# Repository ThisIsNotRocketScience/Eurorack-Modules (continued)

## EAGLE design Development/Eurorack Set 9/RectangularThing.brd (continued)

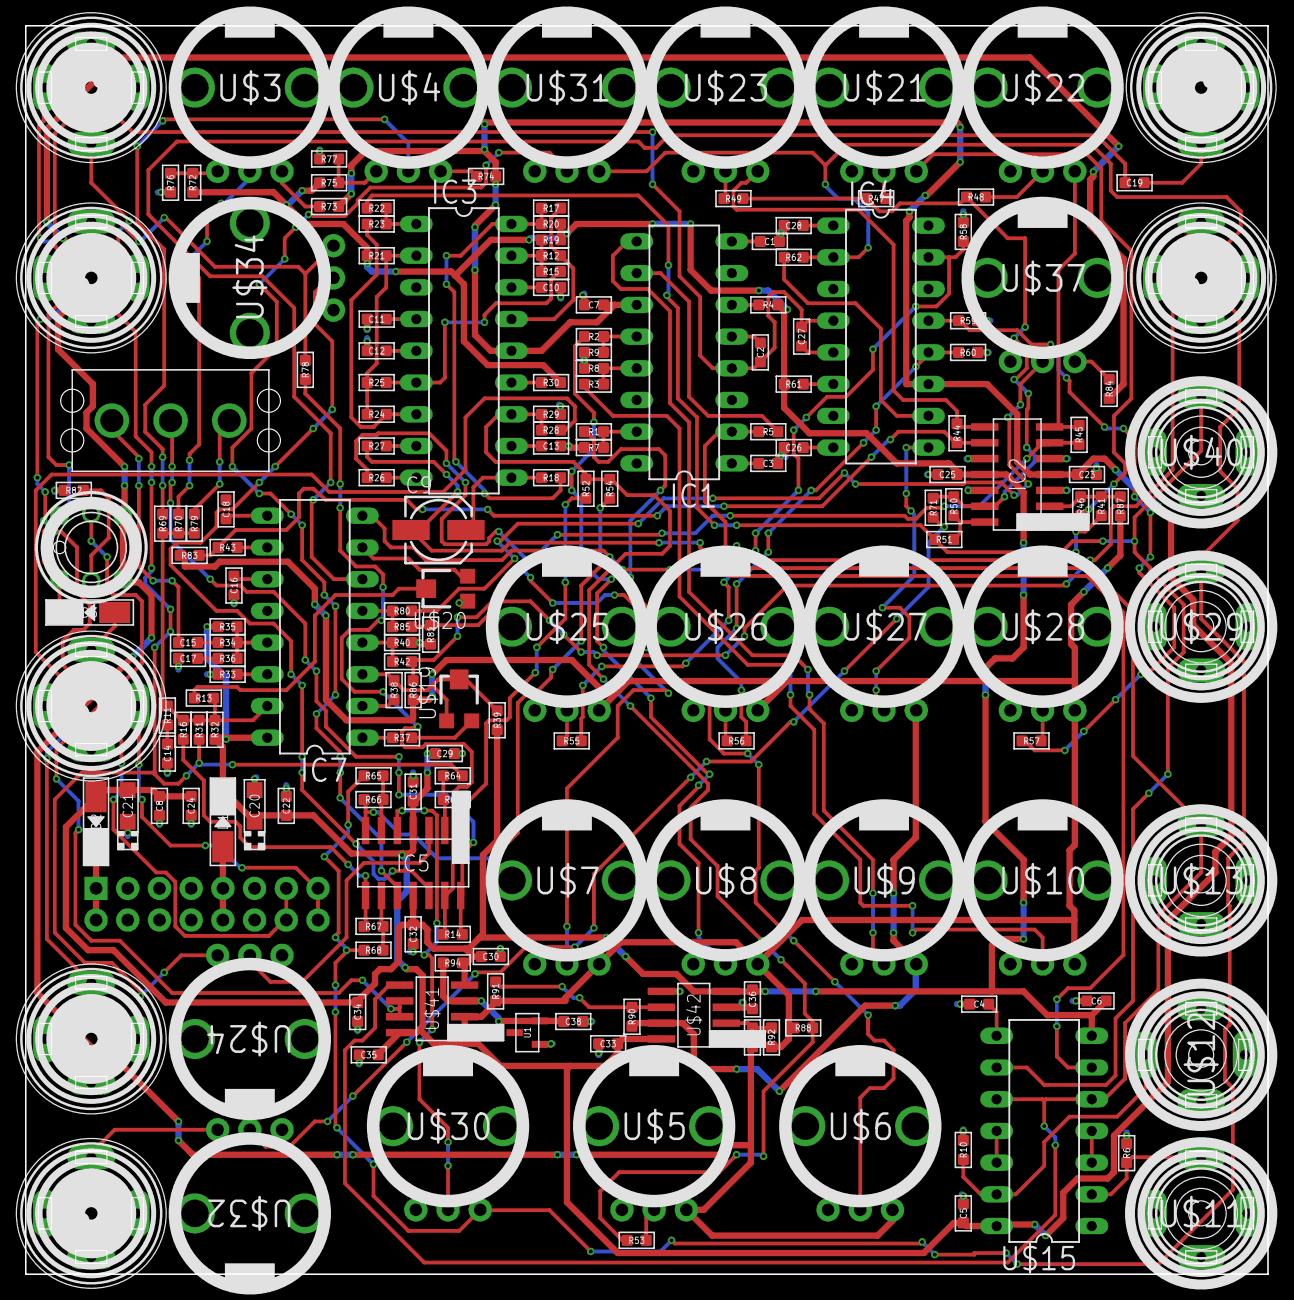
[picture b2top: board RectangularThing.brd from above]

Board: 2 copper layers, 99.5 x 100.0 mm, 182 parts (1 on the bottom side), 127 nets.

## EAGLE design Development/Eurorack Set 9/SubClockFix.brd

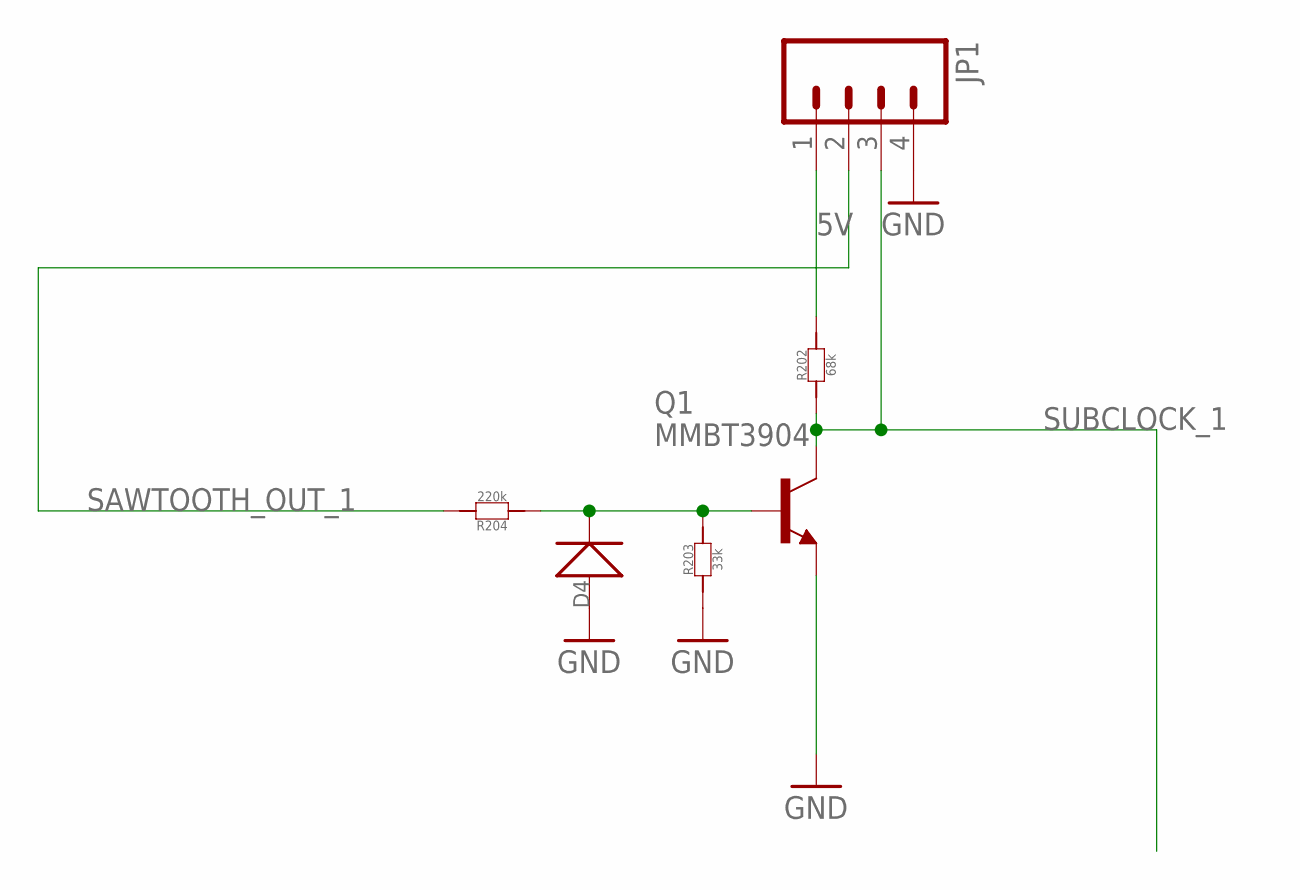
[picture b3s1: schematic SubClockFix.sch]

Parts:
D4: D-SMA; DO-214AC
JP1: M04PTH; 1X04
Q1: MMBT3904; SOT23-BEC; MPN PMBT3904,215
R202: 68k; R0603
R203: 33k; R0603
R204: 220k; R0603

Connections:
5V: JP1.1, R202.2
GND: D4.1 (+), JP1.4, Q1.E, R203.1
unnamed: D4.2 (-), Q1.B, R203.2, R204.1
SAWTOOTH_OUT_1: JP1.2, R204.2
SUBCLOCK_1: JP1.3, Q1.C, R202.1

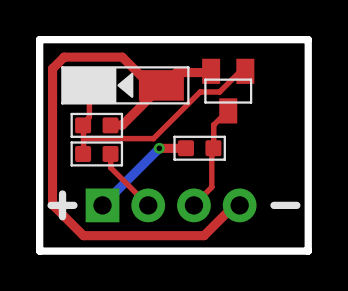
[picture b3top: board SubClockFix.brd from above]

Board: 2 copper layers, 14.9 x 11.7 mm, 6 parts (0 on the bottom side), 5 nets.

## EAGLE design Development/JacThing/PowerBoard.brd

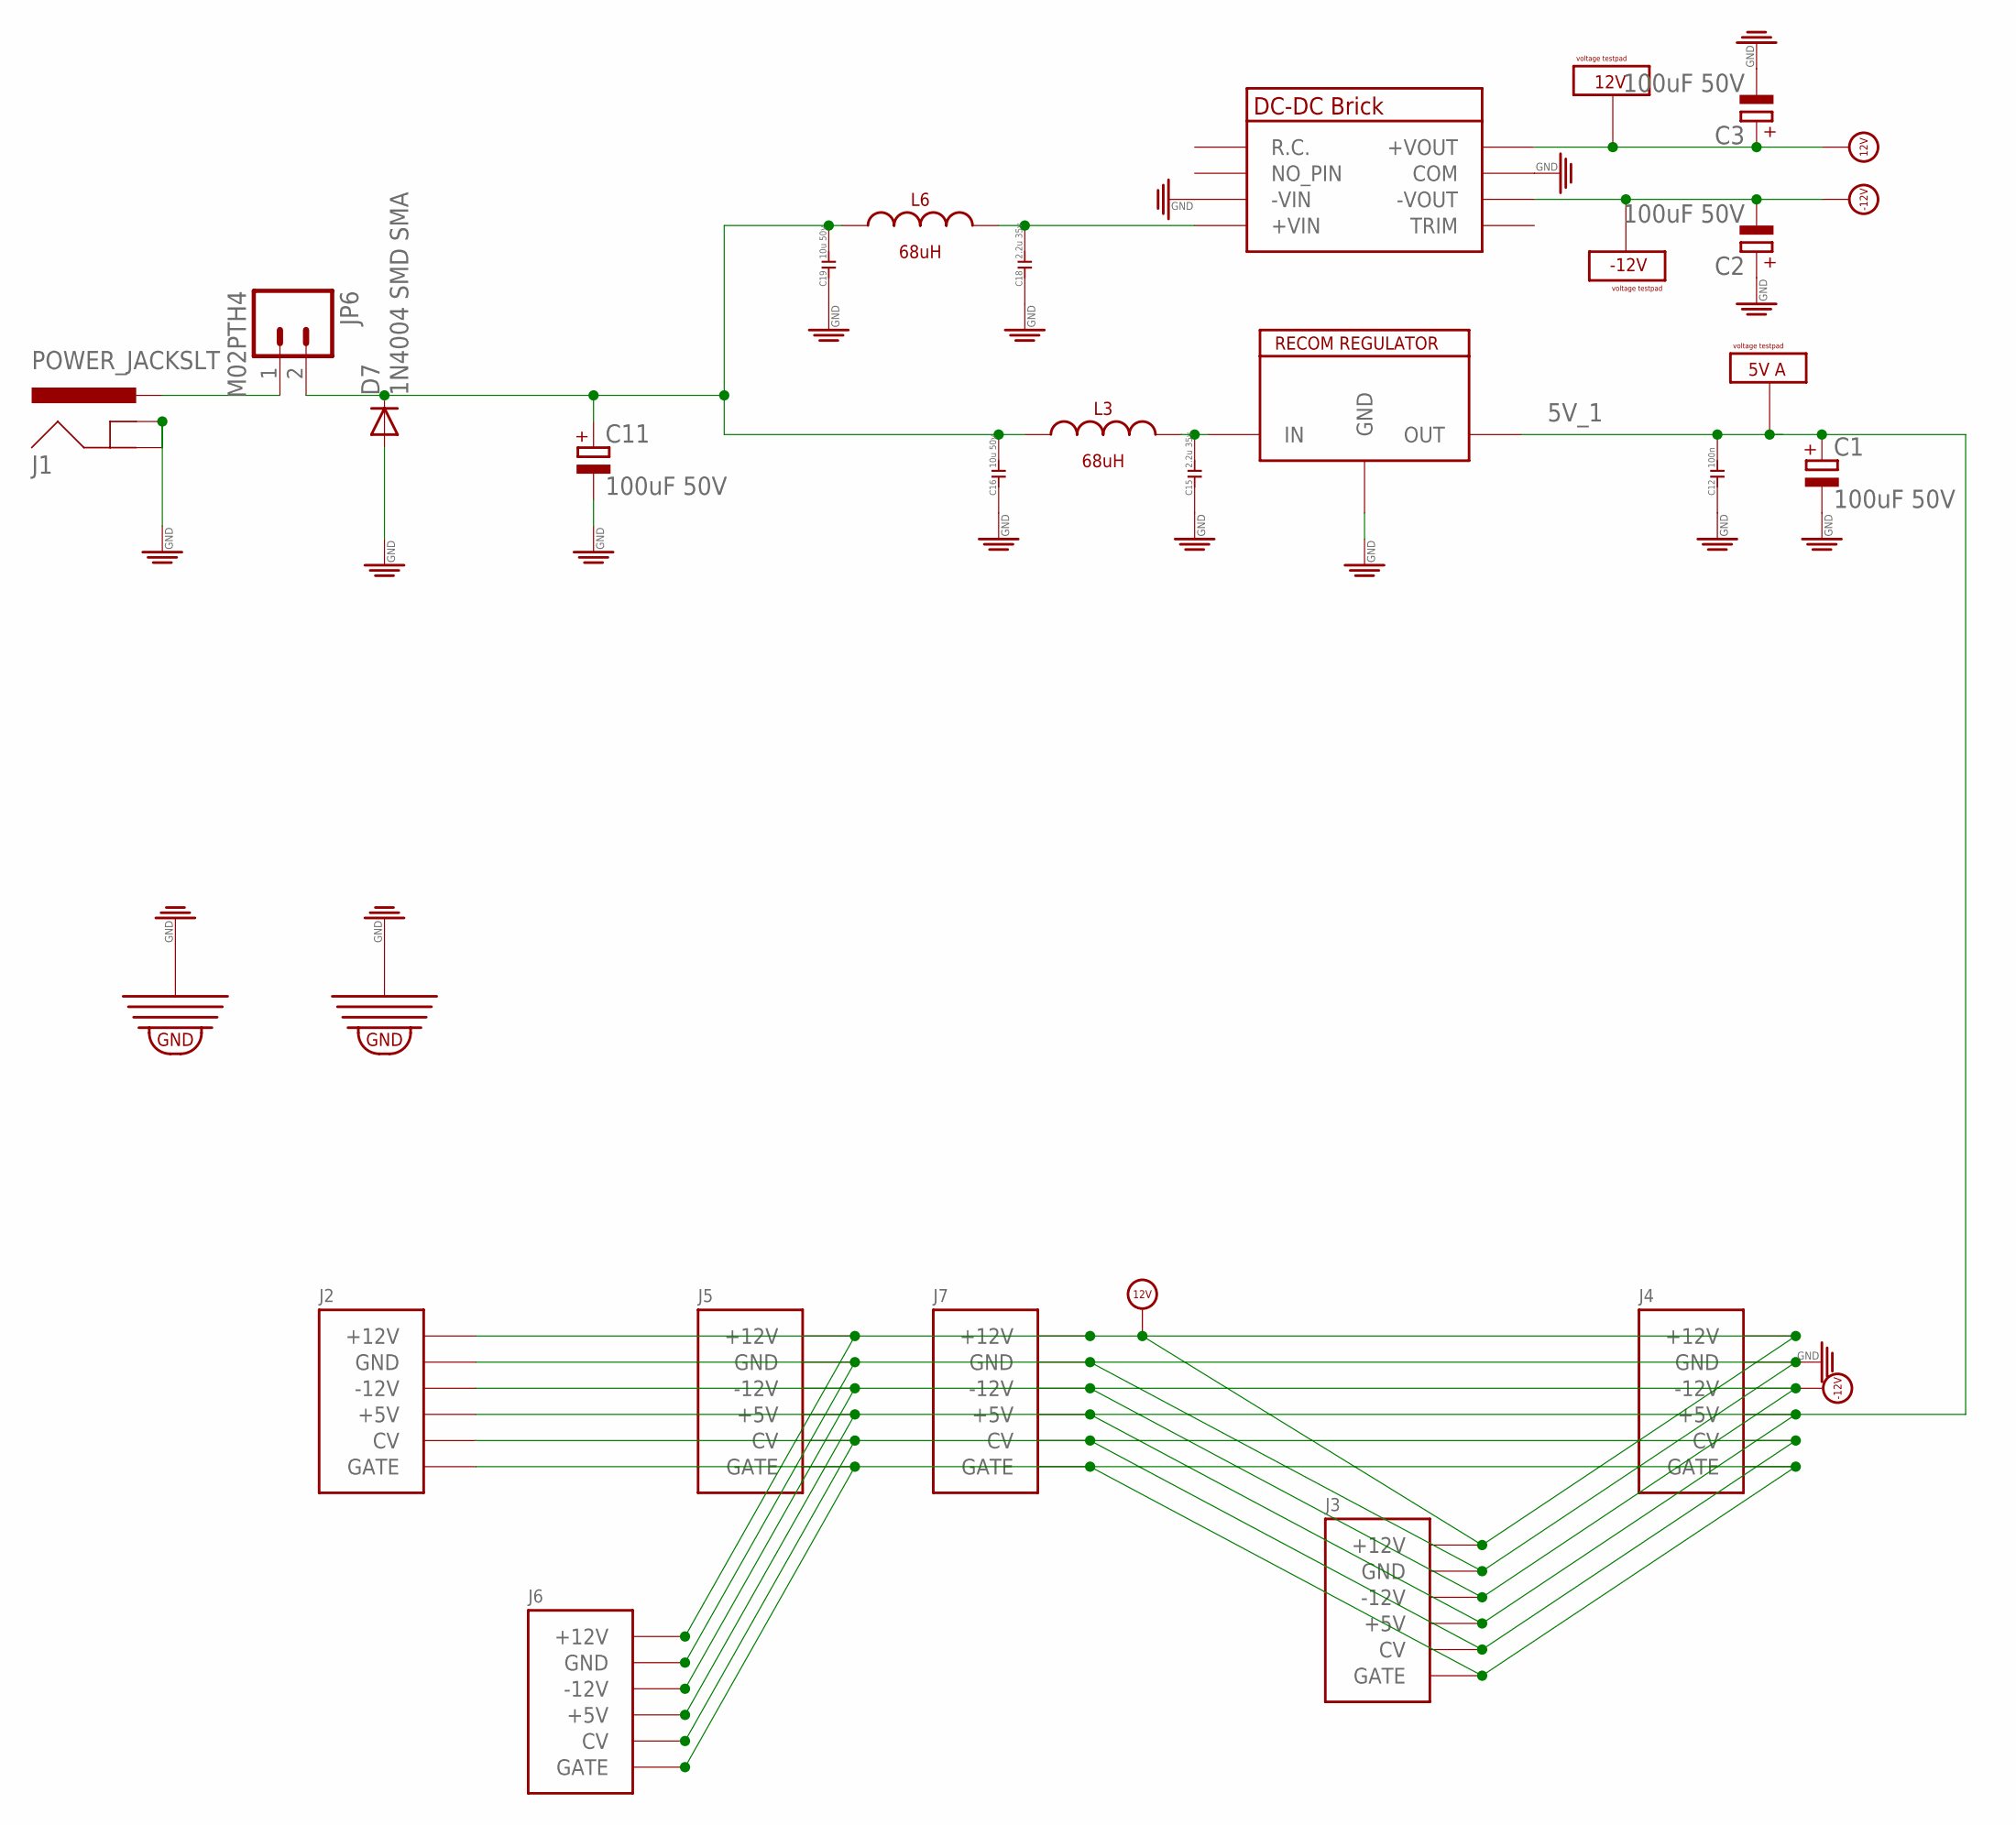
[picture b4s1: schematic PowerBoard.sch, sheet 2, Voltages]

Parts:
C1, C2, C3, C11: 100uF 50V; 153CLV-1010
C12: 100n; C0603
C15, C18: 2.2u 35v; C0603
C16, C19: 10u 50v; C0603
D7: 1N4004 SMD SMA; DO214AC
J1: POWER_JACKSLT; POWER_JACK_SLOT
J2, J3, J4, J5, J6, J7: POWERSHROUDED; POWER_16_SHROUDED
JP6: M02PTH4; 1X02_XTRA_BIG
L3, L6: 68uH; SWRB120XS
U$1: DKA30; MEANWELL_DKA30
U$17: RECOM_REGULATOR; R-78E5.0-1.0
U$19, U$22: GNDLOOP; GROUNDLOOP
U$23, U$25, U$28: VOLTAGETESTPAD; POWERTESTPAD

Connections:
5V_1: C1.+, C12.2, J2.11 (+5V), J2.12 (+5V), J3.11 (+5V), J3.12 (+5V), J4.11 (+5V), J4.12 (+5V), J5.11 (+5V), J5.12 (+5V), J6.11 (+5V), J6.12 (+5V), J7.11 (+5V), J7.12 (+5V), U$17.P$3 (OUT), U$25.P$1, U$25.P$2, U$25.P$3
9TO18V: C11.+, C16.2, C19.2, D7.C, JP6.2, L3.P$1, L6.P$1
12V: C3.+, J2.9 (+12V), J2.10 (+12V), J3.9 (+12V), J3.10 (+12V), J4.9 (+12V), J4.10 (+12V), J5.9 (+12V), J5.10 (+12V), J6.9 (+12V), J6.10 (+12V), J7.9 (+12V), J7.10 (+12V), U$1.P$5 (+VOUT), U$23.P$1, U$23.P$2, U$23.P$3
-12V: C2.-, J2.1 (-12V), J2.2 (-12V), J3.1 (-12V), J3.2 (-12V), J4.1 (-12V), J4.2 (-12V), J5.1 (-12V), J5.2 (-12V), J6.1 (-12V), J6.2 (-12V), J7.1 (-12V), J7.2 (-12V), U$1.P$7 (-VOUT), U$28.P$1, U$28.P$2, U$28.P$3
GND: C1.-, C2.+, C3.-, C11.-, C12.1, C15.1, C16.1, C18.1, C19.1, D7.A, J1.GND@1 (GNDBREAK), J1.GND@2 (GND), J2.3 (GND), J2.4 (GND), J2.5 (GND), J2.6 (GND), J2.7 (GND), J2.8 (GND), J3.3 (GND), J3.4 (GND), J3.5 (GND), J3.6 (GND), J3.7 (GND), J3.8 (GND), J4.3 (GND), J4.4 (GND), J4.5 (GND), J4.6 (GND), J4.7 (GND), J4.8 (GND), J5.3 (GND), J5.4 (GND), J5.5 (GND), J5.6 (GND), J5.7 (GND), J5.8 (GND), J6.3 (GND), J6.4 (GND), J6.5 (GND), J6.6 (GND), J6.7 (GND), J6.8 (GND), J7.3 (GND), J7.4 (GND), J7.5 (GND), J7.6 (GND), J7.7 (GND), J7.8 (GND), U$1.P$3 (-VIN), U$1.P$6 (COM), U$17.P$2 (GND), U$19.P$1, U$19.P$2, U$22.P$1, U$22.P$2
unnamed: J1.PWR, JP6.1
unnamed: J2.13 (CV), J2.14 (CV), J3.13 (CV), J3.14 (CV), J4.13 (CV), J4.14 (CV), J5.13 (CV), J5.14 (CV), J6.13 (CV), J6.14 (CV), J7.13 (CV), J7.14 (CV)
unnamed: J2.15 (GATE), J2.16 (GATE), J3.15 (GATE), J3.16 (GATE), J4.15 (GATE), J4.16 (GATE), J5.15 (GATE), J5.16 (GATE), J6.15 (GATE), J6.16 (GATE), J7.15 (GATE), J7.16 (GATE)
unnamed: C18.2, L6.P$2, U$1.P$4 (+VIN)
unnamed: C15.2, L3.P$2, U$17.P$1 (IN)

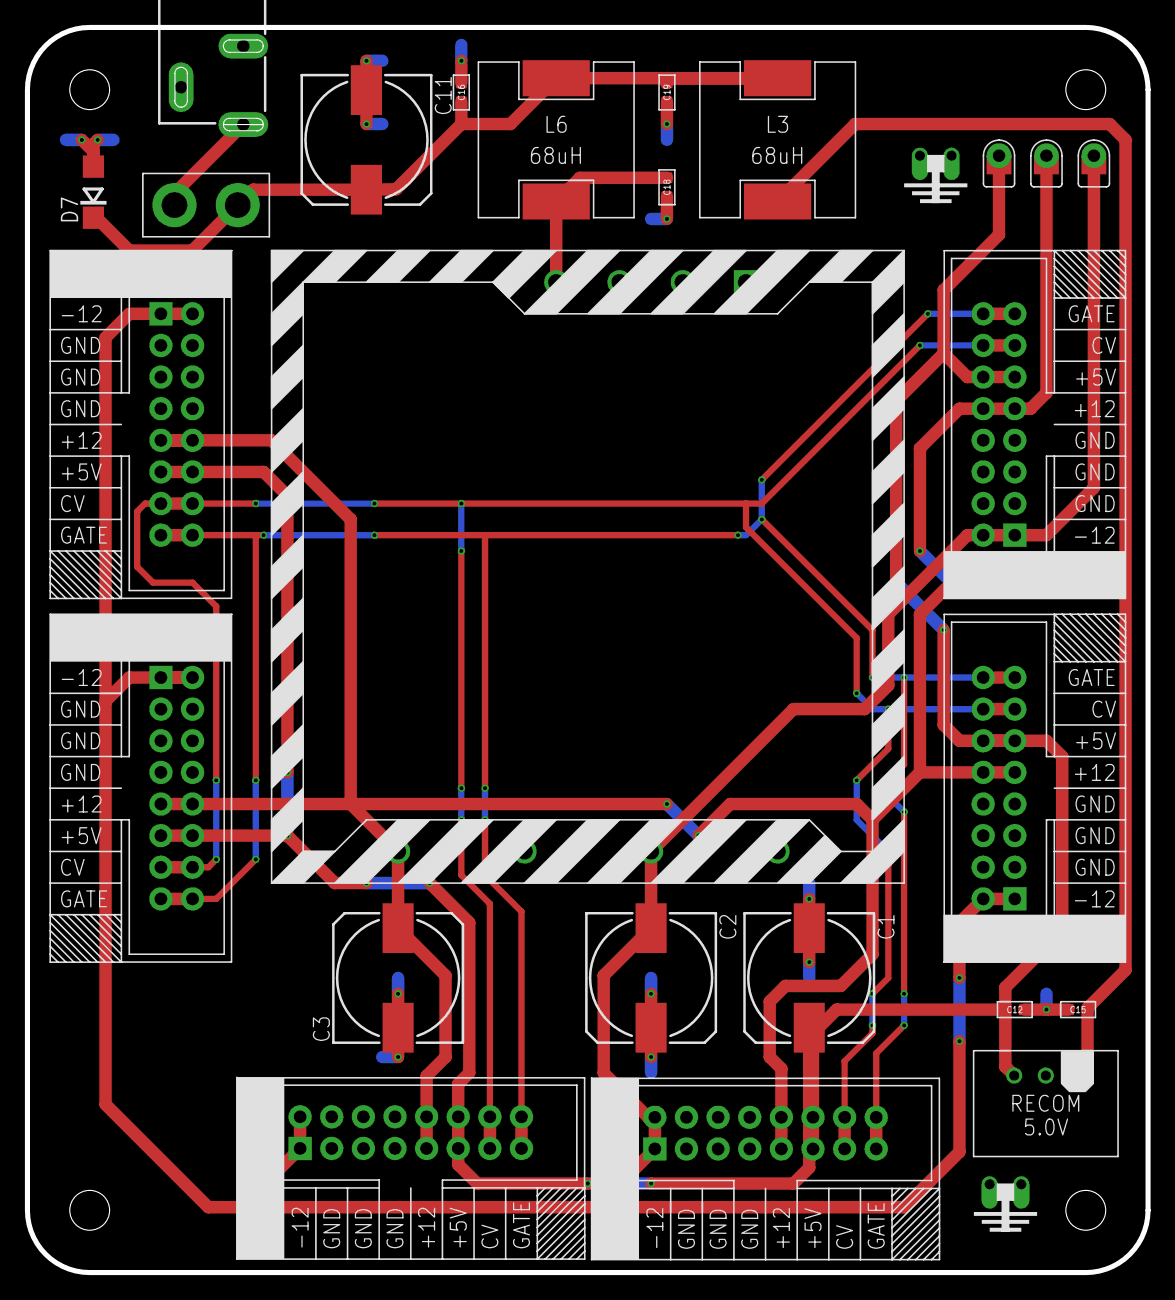
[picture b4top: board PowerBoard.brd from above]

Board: 2 copper layers, 90.0 x 100.0 mm, 27 parts (0 on the bottom side), 10 nets.

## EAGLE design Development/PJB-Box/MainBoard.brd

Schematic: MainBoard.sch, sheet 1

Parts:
C1, C2, C26, C27: 100n; C0603
C3, C4, C5, C10, C15, C16: 3.3nF; C0603
C6, C8, C18, C19: 100nF; C0603; MPN MC0603F104Z160CT
C20, C22: 100u; PANASONIC_D
C21: 22p; C0603
D1: BAS16W; SOT-323
IC2: NE5532D; SO08
IC3: TL074D; SO14; MPN TL074CD
IC4: MCP6004; SO14; MPN MCP6004-I/SL.
J2: POWER_SHROUDED_NOTEXT; POWER_16_SHROUDED_NOTEXT
J4, J5: POWERSHROUDED; POWER_16_SHROUDED
JP1: AUDIO-JACK4-.25-HORIZ-TRS; AUDIO-JACK-.25-INCH-HORIZ-PTH
JP2, JP3, JP4, JP5: PINHD-1X3; 1X03
JP7, JP8: PINHD-1X14; 1X14
L1, L2: FERRITE - 600R/100MHZ; L0603
MAINTEENSY: TEENSY_LC_ALL_PINS; TEENSY_3.0-3.2&LC_ALL_PINS
Q1, Q2, Q3, Q4, Q5, Q6, Q7: MMBT3904; SOT23-BEC; MPN PMBT3904,215
R1, R11, R13, R19, R20: 220; R0603
R2, R4, R9, R14, R16, R18, R22, R39: 10k; R0603
R3, R6, R15, R17, R21, R23, R36, R37, R38, R40, R43, R48, R52, R53, R55: 100k; R0603
R5: 1k; R0603
R7, R8: 4.7k; R0603
R10: 56k; R0603
R12: 27; R0603
R24, R26: 30k; R0603
R25, R27: 12k; R0603
R28, R35: 100; R0603
R41, R44, R46, R47, R49, R51, R56, R58: 33k; R0603
R42, R45, R50, R57: 51k; R0603
SECONDTEENSY: TEENSY_LC_ALL_PINS; TEENSY_3.0-3.2&LC_ALL_PINS
U7: MCP4822-E/SN; SOIC8-N_MC
U$1: M08X2; 2X8
U$3, U$5, U$30, U$32: VOLTAGETESTPAD; POWERTESTPAD
U$4: MIDIJACK; CP-2350
U$17: HEARTOFGOLD
U$19, U$22: GNDLOOP; GROUNDLOOP
U$20: 6N139S; 8DIPSMD
X1, X3: USB-A-FEMALERECEPTACLE; FCI87520
X2, X4: USB-B-FEMALE; FCI61729

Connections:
3.3V: C2.2, C6.2, C8.2, IC4.4 (V+), JP2.3, JP3.3, JP4.3, JP5.3, MAINTEENSY.3.3V, MAINTEENSY.3.3V1 (3.3V), R5.2, U7.1 (VDD), U$20.8 (VCC)
5V: J2.11 (+5V), J2.12 (+5V), J4.11 (+5V), J4.12 (+5V), J5.11 (+5V), J5.12 (+5V), MAINTEENSY.VIN, SECONDTEENSY.VIN; also elsewhere on the board
12V: C18.2, C26.2, IC2.8 (V+), IC3.4 (V+), J2.9 (+12V), J2.10 (+12V), J4.9 (+12V), J4.10 (+12V), J5.9 (+12V), J5.10 (+12V), R2.2, R4.2, R14.2, R16.2, R18.2, R22.2, R39.2, U$1.13; also elsewhere on the board
-12V: C19.2, C27.1, IC2.4 (V-), IC3.11 (V-), J2.1 (-12V), J2.2 (-12V), J4.1 (-12V), J4.2 (-12V), J5.1 (-12V), J5.2 (-12V), U$1.12; also elsewhere on the board
CLOCK1: Q3.C, R14.1, U$1.9
CLOCK2: Q4.C, R16.1, U$1.7
CLOCK3: Q6.C, R18.1, U$1.1
CV1: J5.13 (CV), J5.14 (CV), R28.1, U$1.10
CV2: J2.13 (CV), J2.14 (CV), J4.13 (CV), J4.14 (CV), R35.1, U$1.6
DACCS: MAINTEENSY.15/A1 (15/A1/T), U7.2 (/CS)
DACSCK: MAINTEENSY.13 (13/SCK/LED), U7.3 (SCK)
DACSDI: MAINTEENSY.11 (11/MOSI), U7.4 (SDI)
G1: J5.15 (GATE), J5.16 (GATE), Q5.C, R39.1, U$1.8
G2: J2.15 (GATE), J2.16 (GATE), J4.15 (GATE), J4.16 (GATE), Q1.C, R2.1, U$1.4
G3: Q2.C, R4.1, U$1.2
GND: C1.1, C2.1, C6.1, C8.1, C18.1, C19.1, C26.1, C27.2, IC3.3 (+IN), IC3.5 (+IN), IC3.10 (+IN), IC3.12 (+IN), IC4.3 (+IN), IC4.5 (+IN), IC4.10 (+IN), IC4.11 (V-), IC4.12 (+IN), J2.3 (GND), J2.4 (GND), J2.5 (GND), J2.6 (GND), J2.7 (GND), J2.8 (GND), J4.3 (GND), J4.4 (GND), J4.5 (GND), J4.6 (GND), J4.7 (GND), J4.8 (GND), J5.3 (GND), J5.4 (GND), J5.5 (GND), J5.6 (GND), J5.7 (GND), J5.8 (GND), JP1.P$2 (EARTH), JP1.P$3 (EARTH-NORM), JP1.P$4 (RING), JP2.1, JP3.1, JP4.1, JP5.1, MAINTEENSY.AGND (GND), MAINTEENSY.GND, MAINTEENSY.GND1 (GND), Q1.E, Q2.E, Q3.E, Q4.E, Q5.E, Q6.E, Q7.E, R9.1, R10.2, R12.2, SECONDTEENSY.AGND (GND), SECONDTEENSY.GND, SECONDTEENSY.GND1 (GND), U7.5 (/LDAC), U7.7 (VSS), U$1.15, U$1.16, U$19.P$1, U$19.P$2, U$20.5 (GND), U$22.P$1, U$22.P$2, X1.P4 (GND), X1.P$1 (GND1), X1.P$2 (GND2), X2.4 (GND), X2.P$1 (GND1), X2.P$2 (GND2), X3.P4 (GND), X3.P$1 (GND1), X3.P$2 (GND2), X4.4 (GND), X4.P$1 (GND1), X4.P$2 (GND2); also elsewhere on the board
KNOB_L1: JP3.2, R46.2
KNOB_L2: JP5.2, R47.2
KNOB_X1: JP2.2, R51.2
KNOB_X2: JP4.2, R58.2
L1: R38.2, U$1.5
L1_ADC: C15.2, IC4.8 (OUT), JP8.4, MAINTEENSY.16/A2 (16/A2/PWM/T), R41.1, SECONDTEENSY.16/A2 (16/A2/PWM/T)
L2: R43.2, U$1.11
L2_ADC: C5.2, IC4.1 (OUT), JP8.5, MAINTEENSY.17/A3 (17/A3/PWM/T), R44.1, SECONDTEENSY.17/A3 (17/A3/PWM/T)
MAIN_TO_SECOND: JP7.9, MAINTEENSY.8 (8/TX3), SECONDTEENSY.7 (7/RX3)
MIDI: MAINTEENSY.9 (9/RX2/PWM), R5.1, U$20.6 (VO), U$30.P$1, U$30.P$2, U$30.P$3
unnamed: R9.2, U$20.7 (VB)
unnamed: C20.-, C22.-
unnamed: L1.2, U$4.5
unnamed: L2.2, U$4.4
unnamed: MAINTEENSY.VBAT (17_AT_VIN), U$3.P$1, U$3.P$2, U$3.P$3
unnamed: SECONDTEENSY.VBAT (17_AT_VIN), U$5.P$1, U$5.P$2, U$5.P$3
unnamed: C21.1, IC2.6 (-IN), R7.1, R8.2
unnamed: C20.+, C21.2, IC2.7 (OUT), R8.1
unnamed: C22.+, R10.1, R11.1, R13.1, R19.1, R20.1
unnamed: IC2.5 (+IN), R12.1
unnamed: Q1.B, R3.2
unnamed: Q2.B, R6.2
unnamed: Q3.B, R15.2
unnamed: Q4.B, R17.2
unnamed: Q6.B, R21.2
unnamed: Q7.B, R23.2
unnamed: C4.2, IC3.1 (OUT), R26.1, R36.1
unnamed: C3.2, IC3.14 (OUT), R24.1, R53.1
unnamed: C3.1, IC3.13 (-IN), R24.2, R27.1
unnamed: C4.1, IC3.2 (-IN), R25.1, R26.2
unnamed: C10.1, IC4.6 (-IN), R55.1, R56.2, R57.1, R58.1
unnamed: JP7.2, SECONDTEENSY.0 (0/RX1/T/MOSI1)
unnamed: IC3.6 (-IN), R36.2, R37.1
unnamed: IC3.7 (OUT), R28.2, R37.2
unnamed: IC3.9 (-IN), R52.1, R53.2
unnamed: R27.2, U7.8 (VOUTA)
unnamed: R25.2, U7.6 (VOUTB)
unnamed: JP7.3, SECONDTEENSY.1 (1/TX1/T/MISO1)
unnamed: C1.2, U$4.2
unnamed: L2.1, R1.1
unnamed: D1.ANODE, L1.1, U$20.3 (CATHODE)
unnamed: D1.CATHODE, R1.2, U$20.2 (ANODE)
unnamed: C15.1, IC4.9 (-IN), R38.1, R41.2, R42.1, R46.1
unnamed: JP7.4, SECONDTEENSY.2
unnamed: C5.1, IC4.2 (-IN), R43.1, R44.2, R45.1, R47.1
unnamed: JP7.5, SECONDTEENSY.3 (3/T/PWM)
unnamed: C16.1, IC4.13 (-IN), R48.1, R49.2, R50.1, R51.1
unnamed: JP7.6, SECONDTEENSY.4 (4/T/PWM)
unnamed: JP7.7, SECONDTEENSY.5
unnamed: JP7.8, SECONDTEENSY.6 (6/PWM)
unnamed: JP7.11, SECONDTEENSY.9 (9/RX2/PWM)
unnamed: JP7.12, SECONDTEENSY.10 (10/TX2/PWM)
unnamed: JP7.13, SECONDTEENSY.11 (11/MOSI)
unnamed: JP7.14, SECONDTEENSY.12 (12/MISO)
unnamed: JP8.1, SECONDTEENSY.13 (13/SCK/LED)
unnamed: JP8.2, SECONDTEENSY.14/A0
unnamed: JP8.3, SECONDTEENSY.15/A1 (15/A1/T)
unnamed: JP8.8, SECONDTEENSY.20/A6 (20/A6/PWM/SCK1)
unnamed: Q5.B, R40.2
unnamed: JP8.9, SECONDTEENSY.21/A7
unnamed: JP8.10, SECONDTEENSY.22/A8 (22/A8/T/PWM/SCL1)
unnamed: JP8.11, SECONDTEENSY.23/A9 (23/A9/T/PWM/SDA1)
unnamed: IC3.8 (OUT), R35.2, R52.2
OUTPUT: R7.2, U$1.14, U$32.P$1, U$32.P$2, U$32.P$3
OUTTIPLEFT: JP1.P$6 (TIP), R11.2, R13.2, R19.2, R20.2
OUT_CLOCK1: MAINTEENSY.5, R15.1
OUT_CLOCK2: MAINTEENSY.6 (6/PWM), R17.1
OUT_CLOCK3: MAINTEENSY.10 (10/TX2/PWM), R21.1
OUT_G1: MAINTEENSY.2, R40.1
OUT_G2: MAINTEENSY.3 (3/T/PWM), R3.1
OUT_G3: MAINTEENSY.4 (4/T/PWM), R6.1
OUT_RESET: MAINTEENSY.14/A0, R23.1
REF_-5V: R42.2, R45.2, R50.2, R57.2; also elsewhere on the board
RESET: Q7.C, R22.1, U$1.3
SECOND_TO_MAIN: JP7.10, MAINTEENSY.7 (7/RX3), SECONDTEENSY.8 (8/TX3)
USB_N: X1.P2 (D-), X2.2 (D-)
USB_N2: X3.P2 (D-), X4.2 (D-)
USB_P: X1.P3 (D+), X2.3 (D+)
USB_P2: X3.P3 (D+), X4.3 (D+)
VUSB: MAINTEENSY.VUSB, X1.P1 (VBUS), X2.1 (VBUS)
VUSB2: SECONDTEENSY.VUSB, X3.P1 (VBUS), X4.1 (VBUS)
X1: R48.2
X1_ADC: C16.2, IC4.14 (OUT), JP8.6, MAINTEENSY.18/A4 (18/A4/T/SDA), R49.1, SECONDTEENSY.18/A4 (18/A4/T/SDA)
X2: R55.2
X2_ADC: C10.2, IC4.7 (OUT), JP8.7, MAINTEENSY.19/A5 (19/A5/T/SCL), R56.1, SECONDTEENSY.19/A5 (19/A5/T/SCL)

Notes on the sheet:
-5.0 to 5.0 -> 3.3 -> 0.0

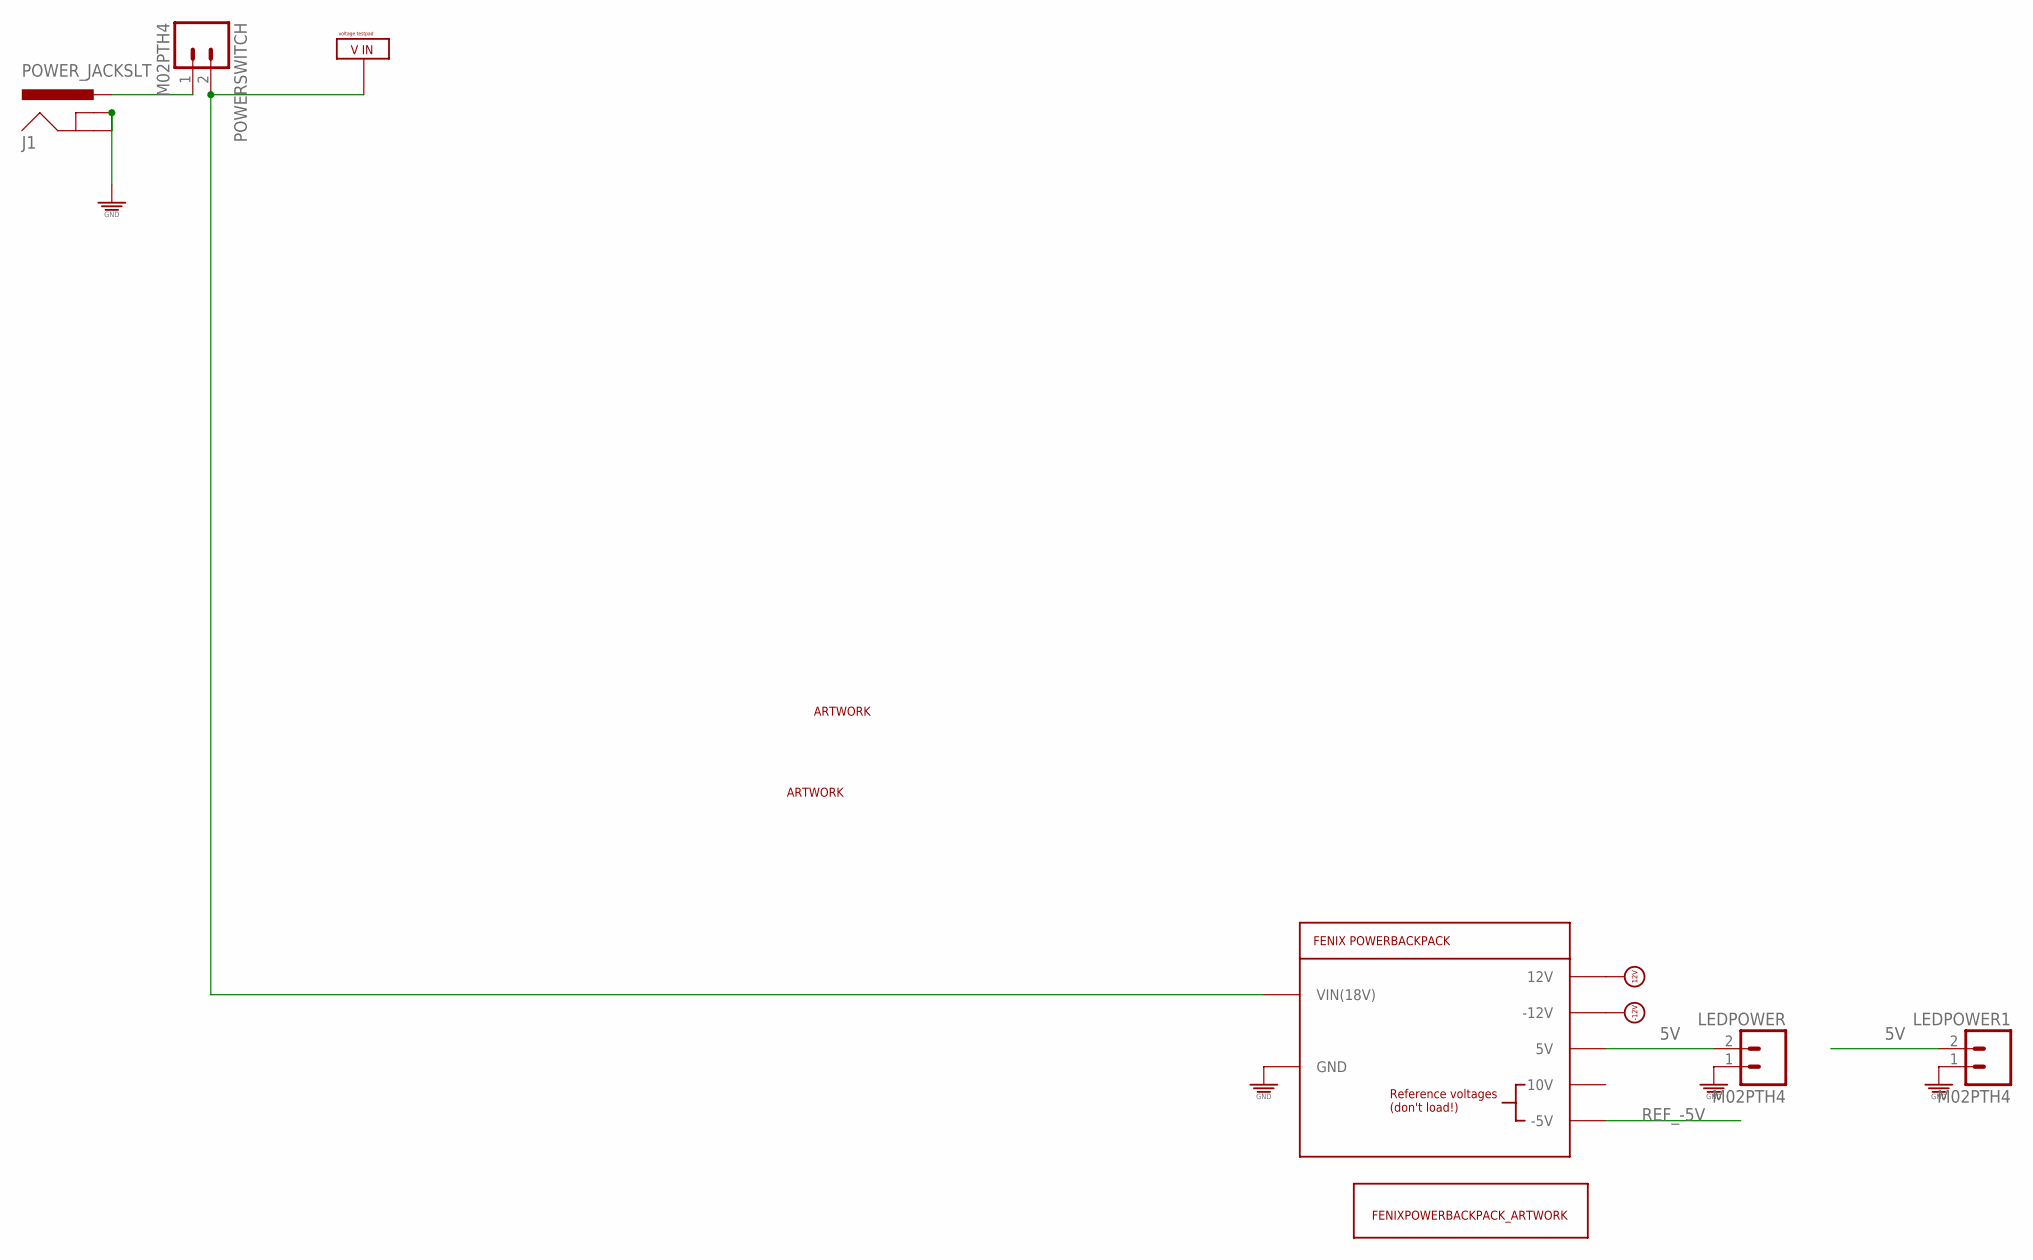
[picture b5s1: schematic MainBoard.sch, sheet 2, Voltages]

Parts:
J1: POWER_JACKSLT; POWER_JACK_SLOT
LEDPOWER, LEDPOWER1: M02PTH4; 1X02_XTRA_BIG
POWERSWITCH: M02PTH4; 1X02_XTRA_BIG
U$23: FENIXPOWERBACKPACK_MODULE; FENIXPOWERBACKPACK
U$25: FENIXPOWERBACKPACKART_MODULE; FENIXPOWERBACKPACK_MODULE
U$29: VOLTAGETESTPAD; POWERTESTPAD
U$34, U$35: TINRS_ARTWORKTINYDATE; JUSTATINYROCKET_DATECODE

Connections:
5V: LEDPOWER.2, LEDPOWER1.2, U$23.5V@1 (5V), U$23.5V@2 (5V), U$23.5V@3 (5V), U$23.5V@4 (5V); also elsewhere on the board
9TO18V: POWERSWITCH.2, U$23.VIN@1 (VIN(18V)), U$23.VIN@2 (VIN(18V)), U$23.VIN@3 (VIN(18V)), U$23.VIN@4 (VIN(18V)), U$29.P$1, U$29.P$2, U$29.P$3
12V: U$23.12V@1 (12V), U$23.12V@2 (12V), U$23.12V@4 (12V); also elsewhere on the board
-12V: U$23.-12V@1 (-12V), U$23.-12V@2 (-12V), U$23.-12V@3 (-12V); also elsewhere on the board
GND: J1.GND@1 (GNDBREAK), J1.GND@2 (GND), LEDPOWER.1, LEDPOWER1.1, U$23.GND@1 (GND), U$23.GND@2 (GND), U$23.GND@3 (GND), U$23.GND@4 (GND), U$23.GND@5 (GND), U$23.GND@6 (GND), U$23.GND@7 (GND), U$23.GND@8 (GND), U$23.GND@9 (GND), U$23.GND@10 (GND), U$23.GND@11 (GND), U$23.GND@12 (GND), U$23.GND@13 (GND), U$23.GND@14 (GND); also elsewhere on the board
REF_-5V: U$23.-5V, U$23.-5V@2 (-5V); also elsewhere on the board
VIN: J1.PWR, POWERSWITCH.1

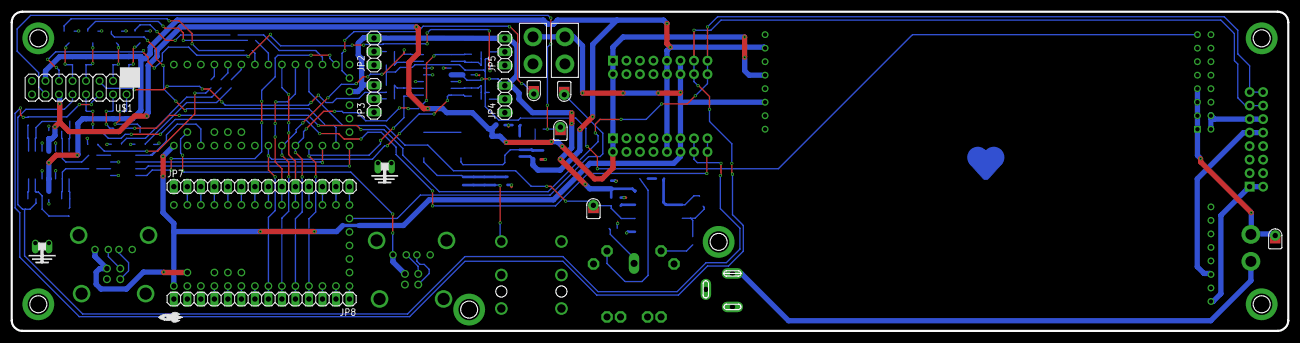
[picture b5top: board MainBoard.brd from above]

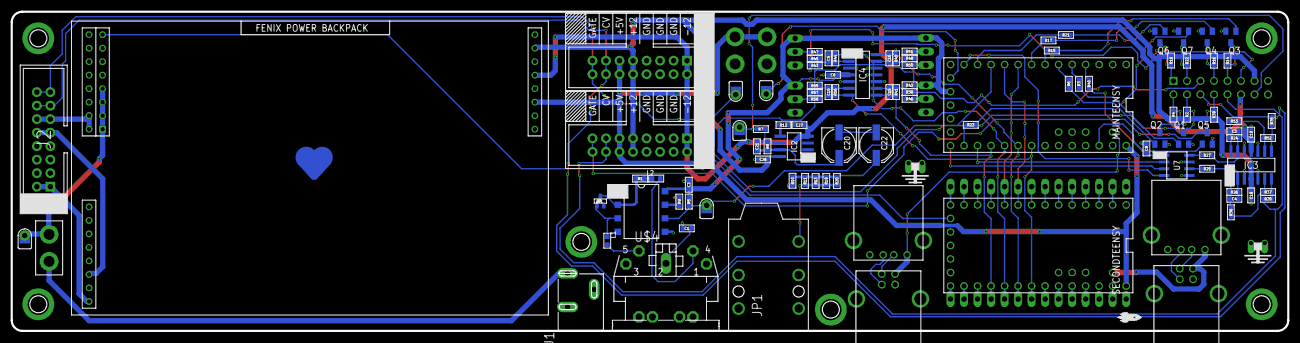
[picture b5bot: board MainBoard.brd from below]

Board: 2 copper layers, 240.0 x 60.0 mm, 117 parts (103 on the bottom side), 101 nets.

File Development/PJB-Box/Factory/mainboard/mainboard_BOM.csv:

Comment,Designator,Footprint,LCSC Part #,combinedname,name
POWER_JACKSLT,"J1",POWER_JACK_SLOT,,POWER_JACK_POWER_JACK_SLOT_POWER_JACKSLT,POWER_JACK
MIDIJACK,"U$4",CP-2350,,MIDIJACK_CP-2350_MIDIJACK,MIDIJACK
USB-A-FEMALERECEPTACLE,"X1, X3",FCI87520,,USB-A-FEMALE_FCI87520_USB-A-FEMALERECEPTACLE,USB-A-FEMALE
USB-B-FEMALE,"X2, X4",FCI61729,,USB-B-FEMALE_FCI61729_USB-B-FEMALE,USB-B-FEMALE
100n,"C1, C2, C26, C27",C0603,,C*_C0603_100n,C*
22p,"C21",C0603,,C*_C0603_22p,C*
3.3nF,"C3, C4, C15, C5, C16, C10",C0603,,C*_C0603_3.3nF,C*
100nF,"C18, C19, C6, C7, C8",C0603,,C*_C0603_100nF,C*
FERRITE - 600R/100MHZ,"L1, L2",L0603,,L*_L0603_FERRITE_-_600R/100MHZ,L*
220,"R1, R11, R13, R19, R20",R0603,,R*_R0603_220,R*
1k,"R5",R0603,,R*_R0603_1k,R*
10k,"R9, R39, R2, R4, R14, R16, R18, R22",R0603,,R*_R0603_10k,R*
4.7k,"R7, R8",R0603,,R*_R0603_4.7k,R*
56k,"R10",R0603,,R*_R0603_56k,R*
27,"R12",R0603,,R*_R0603_27,R*
100k,"R40, R3, R6, R15, R17, R21, R23, R36, R37, R52, R53, R38, R43, R48, R55",R0603,,R*_R0603_100k,R*
30k,"R24, R26",R0603,,R*_R0603_30k,R*
12k,"R25, R27",R0603,,R*_R0603_12k,R*
100,"R28, R35",R0603,,R*_R0603_100,R*
33k,"R41, R44, R46, R47, R49, R51, R56, R58",R0603,,R*_R0603_33k,R*
51k,"R42, R45, R50, R57",R0603,,R*_R0603_51k,R*
6N139S,"U$20",8DIPSMD,,6N139S_8DIPSMD_6N139S,6N139S
,"JP1",AUDIO-JACK-.25-INCH-HORIZ-PTH,,AUDIO-JACK4-.25-HORIZ-TRS_AUDIO-JACK-.25-INCH-HORIZ-PTH_,AUDIO-JACK4-.25-HORIZ-TRS
M02PTH4,"POWERSWITCH, LEDPOWER, LEDPOWER1",1X02_XTRA_BIG,,M02_1X02_XTRA_BIG_M02PTH4,M02
GNDLOOP,"U$19, U$22",GROUNDLOOP,,GNDLOOP_GROUNDLOOP_GNDLOOP,GNDLOOP
VOLTAGETESTPAD,"U$29, U$30, U$32, U$3, U$5",POWERTESTPAD,,VOLTAGETESTPAD_POWERTESTPAD_VOLTAGETESTPAD,VOLTAGETESTPAD
NE5532D,"IC2",SO08,,NE5532_SO08_NE5532D,NE5532
100u,"C20, C22",PANASONIC_D,,CPOL-US_PANASONIC_D_100u,CPOL-US
TINRS_ARTWORKTINYDATE,"U$34, U$35",JUSTATINYROCKET_DATECODE,,TINRS_ARTWORK_JUSTATINYROCKET_DATECODE_TINRS_ARTWORKTINYDATE,TINRS_ARTWORK
BAS16W,"D1",SOT-323,,BAS16W_SOT-323_BAS16W,BAS16W
M08X2,"U$1",2X8,,M08X2_2X8_M08X2,M08X2
TEENSY_LC_ALL_PINS,"MAINTEENSY, SECONDTEENSY",TEENSY_3.0-3.2&LC_ALL_PINS,,TEENSY_LC_ALL_PINS_TEENSY_3.0-3.2&LC_ALL_PINS_TEENSY_LC_ALL_PINS,TEENSY_LC_ALL_PINS
MMBT3904,"Q5, Q1, Q2, Q3, Q4, Q6, Q7",SOT23-BEC,,*-NPN-_SOT23-BEC_MMBT3904,*-NPN-
MCP4822-E/SN,"U7",SOIC8-N_MC,,MCP4822-E/SN_SOIC8-N_MC_MCP4822-E/SN,MCP4822-E/SN
TL074D,"IC3",SO14,,TL074_SO14_TL074D,TL074
MCP6004,"IC4",SO14,,MCP6004_SO14_MCP6004,MCP6004
,"JP2, JP3, JP4, JP5",1X03,,PINHD-1X3_1X03_,PINHD-1X3
,"JP7, JP8",1X14,,PINHD-1X14_1X14_,PINHD-1X14
POWERSHROUDED,"J4, J5",POWER_16_SHROUDED,,POWER_POWER_16_SHROUDED_POWERSHROUDED,POWER
FENIXPOWERBACKPACK_MODULE,"U$23",FENIXPOWERBACKPACK,,FENIXPOWERBACKPACK_FENIXPOWERBACKPACK_FENIXPOWERBACKPACK_MODULE,FENIXPOWERBACKPACK
FENIXPOWERBACKPACKART_MODULE,"U$25",FENIXPOWERBACKPACK_MODULE,,FENIXPOWERBACKPACKART_FENIXPOWERBACKPACK_MODULE_FENIXPOWERBACKPACKART_MODULE,FENIXPOWERBACKPACKART
POWER_SHROUDED_NOTEXT,"J2",POWER_16_SHROUDED_NOTEXT,,POWER_POWER_16_SHROUDED_NOTEXT_POWER_SHROUDED_NOTEXT,POWER
HEARTOFGOLD,"U$17",HEARTOFGOLD,,HEARTOFGOLD_HEARTOFGOLD_HEARTOFGOLD,HEARTOFGOLD
